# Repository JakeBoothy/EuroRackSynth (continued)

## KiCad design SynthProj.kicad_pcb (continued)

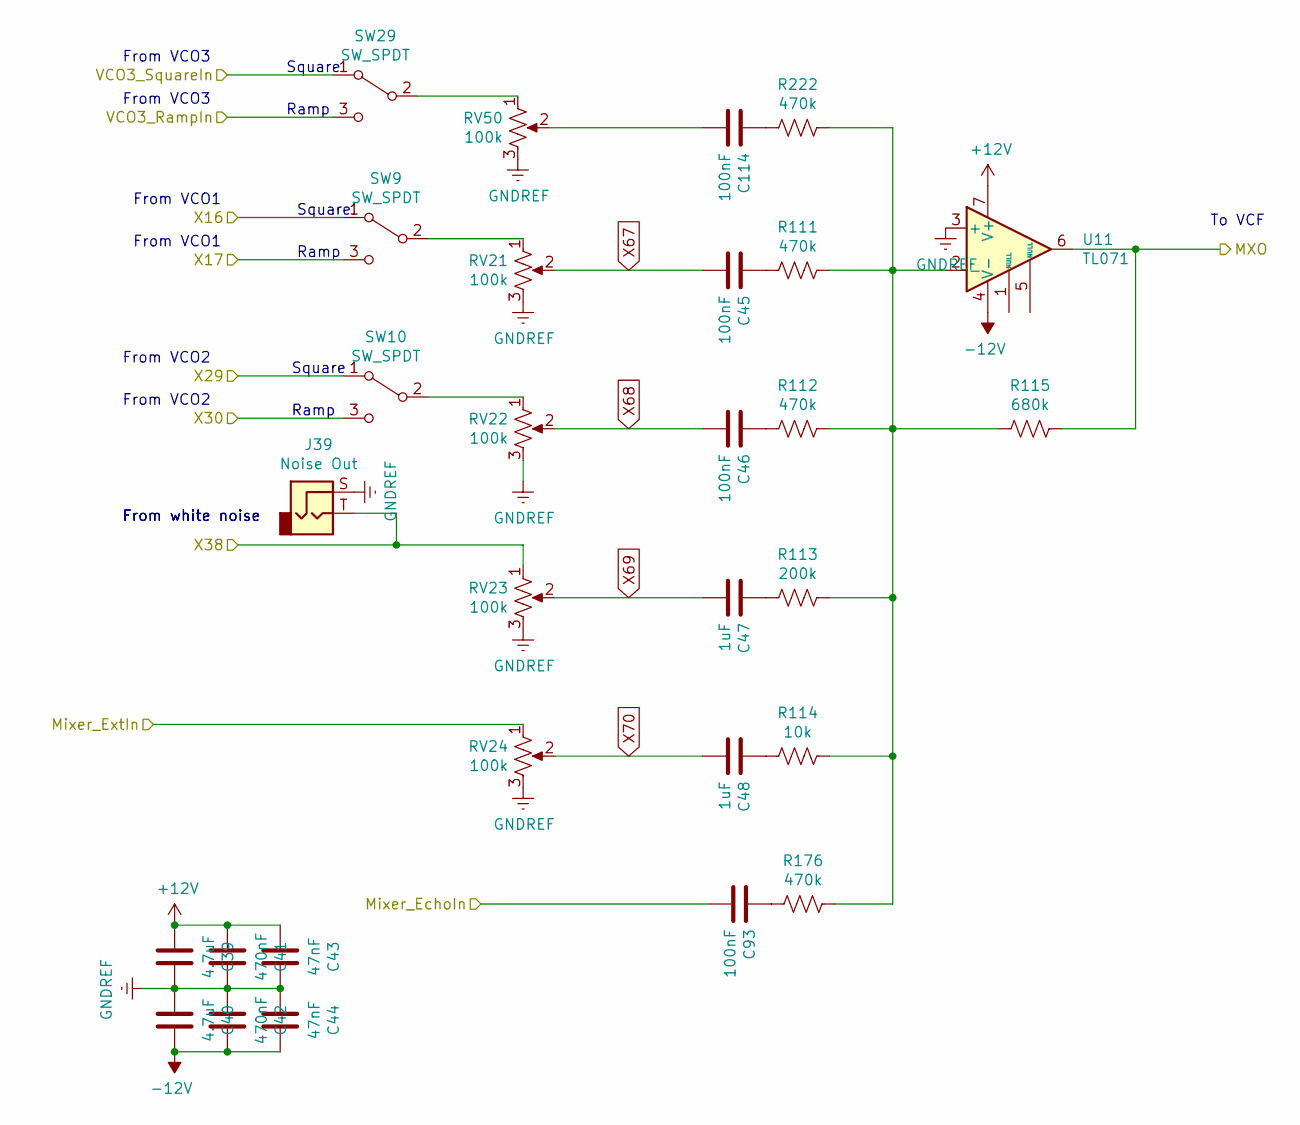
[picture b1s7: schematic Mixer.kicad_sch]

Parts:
C39, C40: 4.7uF; C_0805_2012Metric
C41, C42: 470nF; C_0805_2012Metric
C43, C44: 47nF; C_0603_1608Metric
C45, C46, C93, C114: 100nF; C_0603_1608Metric
C47, C48: 1uF; C_0805_2012Metric
J39: Noise Out; PJ-301-BM
R111, R112, R176, R222: 470k; R_0603_1608Metric
R113: 200k; R_0603_1608Metric
R114: 10k; R_0603_1608Metric
R115: 680k; R_0603_1608Metric
RV21, RV22, RV23, RV24, RV50: 100k; Potentiometer_Alps_RK09K_Single_Vertical
SW9, SW10, SW29: SW_SPDT; SMTS-102
U11: TL071; SO-8_3.9x4.9mm_P1.27mm

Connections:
+12V: C39.2, C41.2, C43.2, U11.7 (V+); also elsewhere on the board
-12V: C40.1, C42.1, C44.1, U11.4 (V-); also elsewhere on the board
/EchoOut: C93.2; also elsewhere on the board
/Mixer/MXO: R115.1, U11.6; also elsewhere on the board
/Mixer/Mixer_ExtIn: RV24.1; also elsewhere on the board
/Mixer/VCO3_RampIn: SW29.3 (C); also elsewhere on the board
/Mixer/VCO3_SquareIn: SW29.1 (A); also elsewhere on the board
/Mixer/X16: SW9.1 (A); also elsewhere on the board
/Mixer/X17: SW9.3 (C); also elsewhere on the board
/Mixer/X29: SW10.1 (A); also elsewhere on the board
/Mixer/X30: SW10.3 (C); also elsewhere on the board
/Mixer/X38: J39.T, RV23.1; also elsewhere on the board
GNDREF: C39.1, C40.2, C41.1, C42.2, C43.1, C44.2, J39.S, RV21.3, RV22.3, RV23.3, RV24.3, RV50.3, U11.3 (+); also elsewhere on the board
unnamed: C45.1, R111.2
unnamed: C46.1, R112.2
unnamed: C47.1, R113.2
unnamed: C48.1, R114.2
unnamed: C93.1, R176.2
unnamed: C114.1, R222.2
unnamed: C114.2, RV50.2
unnamed: RV21.1, SW9.2 (B)
unnamed: RV22.1, SW10.2 (B)
unnamed: RV50.1, SW29.2 (B)
unnamed: R111.1, R112.1, R113.1, R114.1, R115.2, R176.1, R222.1, U11.2 (-)
X67: C45.2, RV21.2
X68: C46.2, RV22.2
X69: C47.2, RV23.2
X70: C48.2, RV24.2

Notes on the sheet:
Ramp
To VCF
From VCO1
From VCO3
Square
From VCO2
From white noise

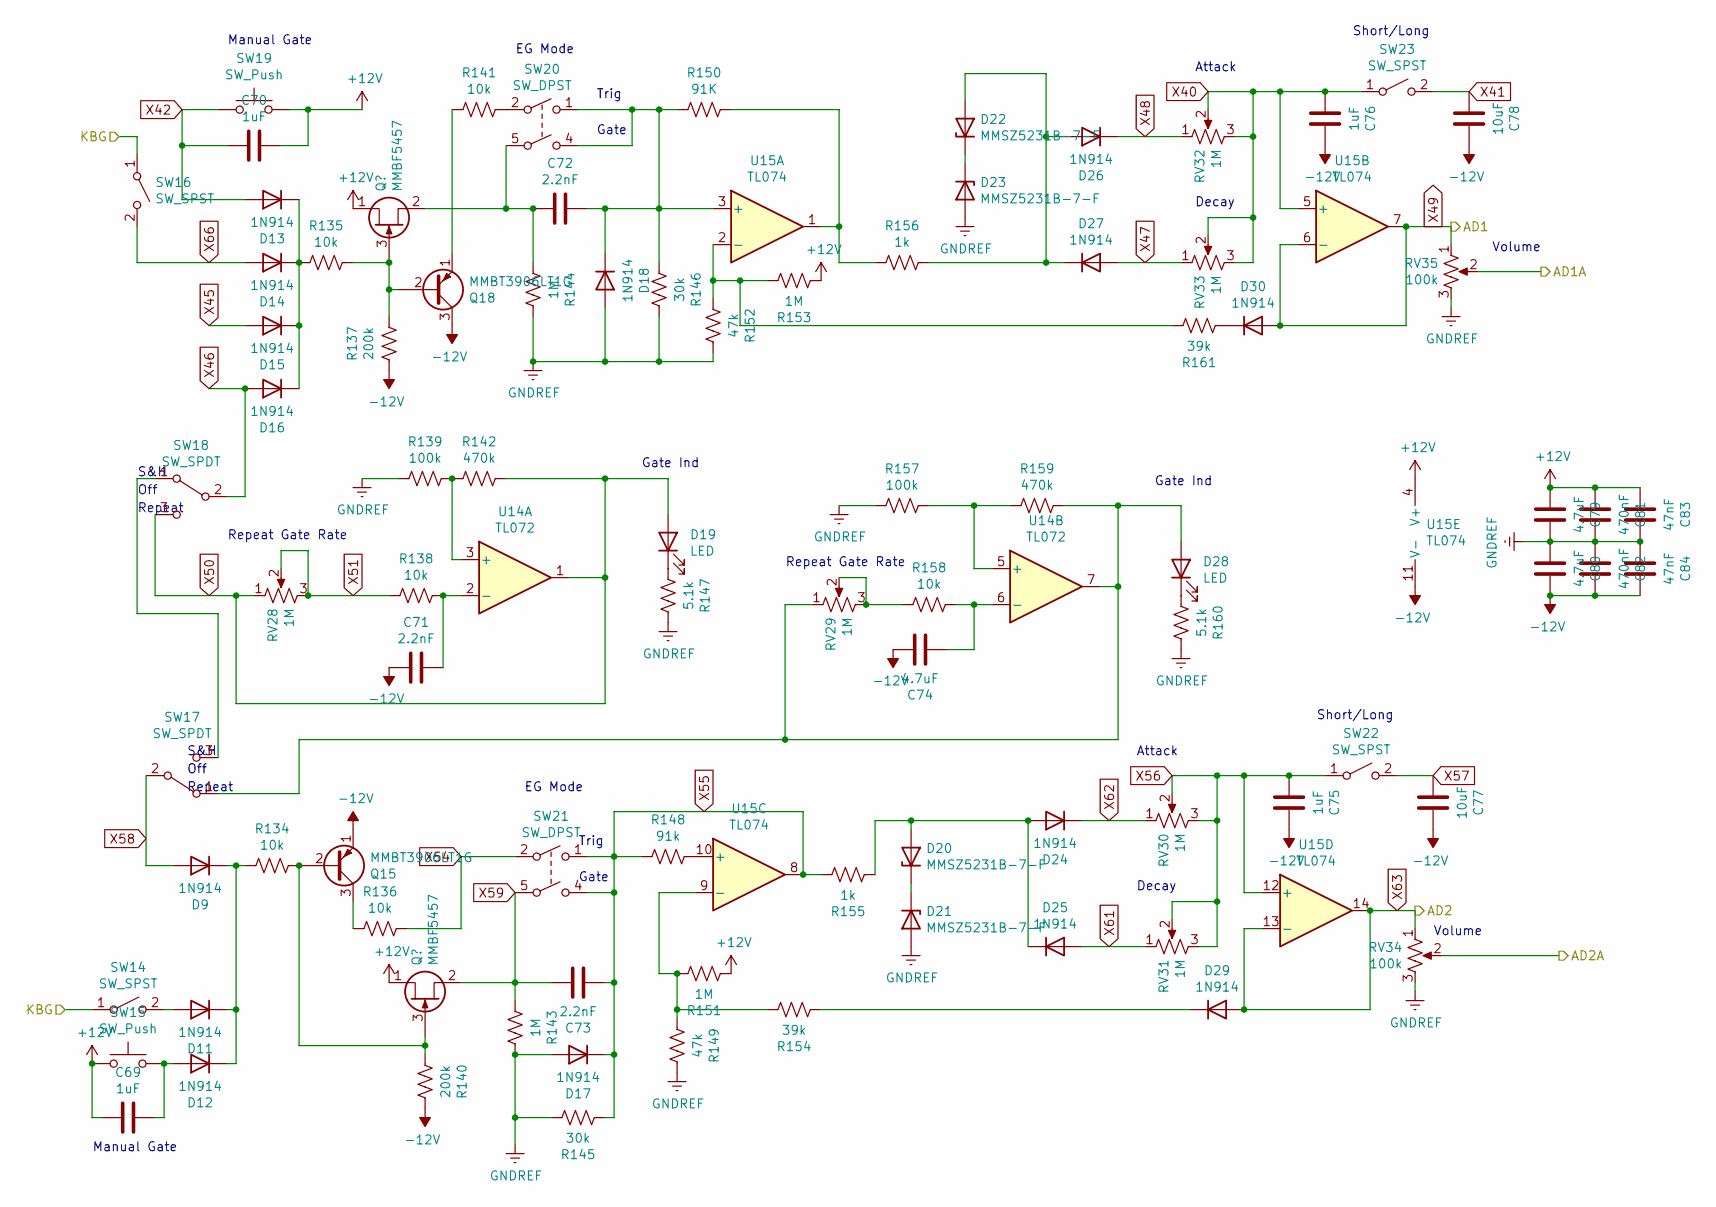
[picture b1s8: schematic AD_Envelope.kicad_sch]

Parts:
C69, C70, C75, C76: 1uF; C_0805_2012Metric
C71, C72, C73: 2.2nF; C_0603_1608Metric
C74, C79, C80: 4.7uF; C_0805_2012Metric
C77, C78: 10uF; C_0805_2012Metric
C81, C82: 470nF; C_0805_2012Metric
C83, C84: 47nF; C_0603_1608Metric
D9, D11, D12, D13, D14, D15, D16, D17, D18, D24, D25, D26, D27, D29, D30: 1N914; D_SOD-323F
D19, D28: LED; LED_0805_2012Metric
D20, D21, D22, D23: MMSZ5231B-7-F; D_SOD-123
Q15, Q18: MMBT3906LT1G; SOT-23-3
Q16, Q17: MMBF5457; SOT-23-3
R134, R135, R136, R138, R141, R158: 10k; R_0603_1608Metric
R137, R140: 200k; R_0603_1608Metric
R139, R157: 100k; R_0603_1608Metric
R142, R159: 470k; R_0603_1608Metric
R143, R144, R151, R153: 1M; R_0603_1608Metric
R145, R146: 30k; R_0603_1608Metric
R147, R160: 5.1k; R_0603_1608Metric
R148: 91k; R_0603_1608Metric
R149, R152: 47k; R_0603_1608Metric
R150: 91K; R_0603_1608Metric
R154, R161: 39k; R_0603_1608Metric
R155, R156: 1k; R_0603_1608Metric
RV28, RV29, RV30, RV31, RV32, RV33: 1M; Potentiometer_Alps_RK09K_Single_Vertical
RV34, RV35: 100k; Potentiometer_Alps_RK09K_Single_Vertical
SW14, SW16, SW22, SW23: SW_SPST; SMTS-102
SW15, SW19: SW_Push; SW_PUSH_6mm_H13mm
SW17, SW18: SW_SPDT; SMTS-102
SW20, SW21: SW_DPST; SMTS-202
U14: TL072; SOP-8_3.9x4.9mm_P1.27mm
U15: TL074; SO-14_3.9x8.65mm_P1.27mm

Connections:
+12V: C69.1, C70.1, C79.2, C81.2, C83.2, Q16.1 (D), Q17.1 (D), R151.2, R153.2, SW15.1, SW19.2, U15.4 (V+); also elsewhere on the board
-12V: C71.2, C74.1, C75.1, C76.1, C77.1, C78.1, C80.1, C82.1, C84.1, Q15.1 (E), Q18.3 (C), R137.2, R140.1, U15.11 (V-); also elsewhere on the board
AD1: D30.2 (A), RV35.1, U15.6 (-), U15.7; also elsewhere on the board
AD1A: RV35.2; also elsewhere on the board
AD2: D29.2 (A), RV34.1, U15.13 (-), U15.14; also elsewhere on the board
AD2A: RV34.2; also elsewhere on the board
GNDREF: C79.1, C80.2, C81.1, C82.2, C83.1, C84.2, D17.2 (A), D18.2 (A), D21.2 (A), D23.2 (A), R139.2, R143.1, R144.1, R145.1, R146.1, R147.1, R149.1, R152.1, R157.2, R160.1, RV34.3, RV35.3; also elsewhere on the board
KBG: SW14.1 (A), SW16.1 (A); also elsewhere on the board
unnamed: D9.1 (K), D11.1 (K), D12.1 (K), R134.2
unnamed: D11.2 (A), SW14.2 (B)
unnamed: C69.2, D12.2 (A), SW15.2
unnamed: D13.1 (K), D14.1 (K), D15.1 (K), D16.1 (K), R135.2
unnamed: C72.1, D18.1 (K), R146.2, R150.2, SW20.1, SW20.4, U15.3 (+)
unnamed: D19.1 (K), R147.2
unnamed: D20.2 (A), D24.2 (A), D25.1 (K), R155.2
unnamed: D20.1 (K), D21.1 (K)
unnamed: D22.2 (A), D26.2 (A), D27.1 (K), R156.1
unnamed: D22.1 (K), D23.1 (K)
unnamed: D28.2 (A), R159.1, RV29.1, SW17.1 (A), U14.7
unnamed: D28.1 (K), R160.2
unnamed: D29.1 (K), R154.2
unnamed: D30.1 (K), R161.2
unnamed: Q15.2 (B), Q17.3 (G), R134.1, R140.2
unnamed: Q15.3 (C), R136.2
unnamed: Q16.3 (G), Q18.2 (B), R135.1, R137.1
unnamed: C72.2, Q16.2 (S), R144.2, SW20.5
unnamed: Q18.1 (E), R141.2
unnamed: R141.1, SW20.2
unnamed: R150.1, R156.2, U15.1
unnamed: R158.2, RV29.2, RV29.3
unnamed: SW17.3 (C), SW18.1 (A)
unnamed: R139.1, R142.2, U14.3 (+)
unnamed: C71.1, R138.1, U14.2 (-)
unnamed: R157.1, R159.2, U14.5 (+)
unnamed: C74.2, R158.1, U14.6 (-)
unnamed: R152.2, R153.1, R161.1, U15.2 (-)
unnamed: R148.1, U15.10 (+)
unnamed: R149.2, R151.1, R154.1, U15.9 (-)
X40: C76.2, RV32.2, RV32.3, RV33.2, RV33.3, SW23.1 (A), U15.5 (+)
X41: C78.2, SW23.2 (B)
X42: C70.2, D13.2 (A), SW19.1
X45: D15.2 (A)
X46: D16.2 (A), SW18.2 (B)
X47: D27.2 (A), RV33.1
X48: D26.1 (K), RV32.1
X50: D19.2 (A), R142.1, RV28.1, SW18.3 (C), U14.1
X51: R138.2, RV28.2, RV28.3
X54: R136.1, SW21.2
X55: C73.2, D17.1 (K), R145.2, R148.2, R155.1, SW21.1, SW21.4, U15.8
X56: C75.2, RV30.2, RV30.3, RV31.2, RV31.3, SW22.1 (A), U15.12 (+)
X57: C77.2, SW22.2 (B)
X58: D9.2 (A), SW17.2 (B)
X59: C73.1, Q17.2 (S), R143.2, SW21.5
X61: D25.2 (A), RV31.1
X62: D24.1 (K), RV30.1
X66: D14.2 (A), SW16.2 (B)

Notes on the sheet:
Gate Ind
S&H
Short/Long
Trig
Volume
EG Mode
Manual Gate
Gate
Decay
Repeat
Attack
Off
Repeat Gate Rate

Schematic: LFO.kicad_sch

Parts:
C61: 22nF; C_0603_1608Metric
C62: 10pF; C_0603_1608Metric
C63, C64: 4.7uF; C_0805_2012Metric
C65, C66: 470nF; C_0805_2012Metric
C67, C68: 47nF; C_0603_1608Metric
D6, D7: 1N914; D_SOD-323F
D8: LED; LED_0805_2012Metric
Q14: MMBT3904-7-F; SOT-23-3
R123: 1k; R_0603_1608Metric
R124, R128: 100k; R_0603_1608Metric
R125: 3M; R_0603_1608Metric
R126: 220; R_0603_1608Metric
R127: 3.9k; R_0603_1608Metric
R129: 2.2k; R_0603_1608Metric
R130: 130k; R_0603_1608Metric
R131: 9.1k; R_0603_1608Metric
R132: 10k; R_0603_1608Metric
R133: 270k; R_0603_1608Metric
RV26: 10k; Potentiometer_Alps_RK09K_Single_Vertical
RV27: 100k; Potentiometer_Alps_RK09K_Single_Vertical
SW11: SW_SPDT; SMTS-102
SW12: SMTS-103-A1-T0; SMTS-102
SW13: SW_Push_DPDT; SMTS-202
U13: TL072; SOP-8_3.9x4.9mm_P1.27mm

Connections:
+12V: C63.2, C65.2, C67.2, R127.1, U13.8 (V+); also elsewhere on the board
-12V: C64.1, C66.1, C68.1, U13.4 (V-); also elsewhere on the board
/LFO/LFO: RV27.1, SW13.5 (B); also elsewhere on the board
GNDREF: C63.1, C64.2, C65.1, C66.2, C67.1, C68.2, D8.1 (K), R126.2, R131.2, RV27.3, U13.2 (-), U13.5 (+); also elsewhere on the board
LFO1A: RV27.2; also elsewhere on the board
unnamed: C61.2, R128.2, R129.2, R130.2, U13.7
unnamed: C62.2, R132.1, R133.1, RV26.1, SW13.2 (B), U13.1
unnamed: D6.2 (A), D7.1 (K), R123.1
unnamed: D6.1 (K), SW12.1 (A)
unnamed: D7.2 (A), SW12.3 (C)
unnamed: D8.2 (A), Q14.1 (E)
unnamed: Q14.2 (B), R128.1
unnamed: Q14.3 (C), R127.2
unnamed: R126.1, RV26.3
unnamed: R129.1, SW13.4 (A)
unnamed: R131.1, R132.2, SW13.6 (C)
unnamed: R124.1, SW11.1 (A)
unnamed: R125.1, RV26.2, SW11.2 (B)
unnamed: SW12.2 (B), SW13.1 (A)
unnamed: C62.1, R130.1, R133.2, U13.3 (+)
unnamed: C61.1, R123.2, R124.2, R125.2, U13.6 (-)

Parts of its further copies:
C106: 22nF; C_0603_1608Metric
C107: 10pF; C_0603_1608Metric
C108, C109: 4.7uF; C_0805_2012Metric
C110, C111: 470nF; C_0805_2012Metric
C112, C113: 47nF; C_0603_1608Metric
D36, D37: 1N914; D_SOD-323F
D38: LED; LED_0805_2012Metric
Q27: MMBT3904-7-F; SOT-23-3
R211: 1k; R_0603_1608Metric
R212, R216: 100k; R_0603_1608Metric
R213: 3M; R_0603_1608Metric
R214: 220; R_0603_1608Metric
R215: 3.9k; R_0603_1608Metric
R217: 2.2k; R_0603_1608Metric
R218: 130k; R_0603_1608Metric
R219: 9.1k; R_0603_1608Metric
R220: 10k; R_0603_1608Metric
R221: 270k; R_0603_1608Metric
RV48: 10k; Potentiometer_Alps_RK09K_Single_Vertical
RV49: 100k; Potentiometer_Alps_RK09K_Single_Vertical
SW26: SW_SPDT; SMTS-102
SW27: SMTS-103-A1-T0; SMTS-102
SW28: SW_Push_DPDT; SMTS-202
U20: TL072; SOP-8_3.9x4.9mm_P1.27mm

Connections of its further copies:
+12V: C108.2, C110.2, C112.2, R215.1, U20.8 (V+); also elsewhere on the board
-12V: C109.1, C111.1, C113.1, U20.4 (V-); also elsewhere on the board
/LFO1/LFO: RV49.1, SW28.5 (B)
GNDREF: C108.1, C109.2, C110.1, C111.2, C112.1, C113.2, D38.1 (K), R214.2, R219.2, RV49.3, U20.2 (-), U20.5 (+); also elsewhere on the board
LFO2A: RV49.2; also elsewhere on the board
unnamed: C106.2, R216.2, R217.2, R218.2, U20.7
unnamed: C107.2, R220.1, R221.1, RV48.1, SW28.2 (B), U20.1
unnamed: D36.2 (A), D37.1 (K), R211.1
unnamed: D36.1 (K), SW27.1 (A)
unnamed: D37.2 (A), SW27.3 (C)
unnamed: D38.2 (A), Q27.1 (E)
unnamed: Q27.2 (B), R216.1
unnamed: Q27.3 (C), R215.2
unnamed: R214.1, RV48.3
unnamed: R217.1, SW28.4 (A)
unnamed: R219.1, R220.2, SW28.6 (C)
unnamed: R212.1, SW26.1 (A)
unnamed: R213.1, RV48.2, SW26.2 (B)
unnamed: SW27.2 (B), SW28.1 (A)
unnamed: C107.1, R218.1, R221.2, U20.3 (+)
unnamed: C106.1, R211.2, R212.2, R213.2, U20.6 (-)

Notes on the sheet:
Triangle
Ramp
Square
Falling
Ramp/Square Select
Rising
Low
SPDT On-Off-On SMTS-103-A1-T0
Range
Ramp Shape

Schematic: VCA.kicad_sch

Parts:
C35, C36: 470nF; C_0805_2012Metric
C37, C38: 10uF; C_0805_2012Metric
R98: 3k; R_0603_1608Metric
R99: 2k; R_0603_1608Metric
R100, R101: 62k; R_0603_1608Metric
R102, R104: 100k; R_0603_1608Metric
R103: 220; R_0603_1608Metric
R105: 110k; R_0603_1608Metric
R106, R109: 10k; R_0603_1608Metric
R107: 4.7k; R_0603_1608Metric
R108: 6.2k; R_0603_1608Metric
R110: 47k; R_0603_1608Metric
RV18, RV19, RV20: 100k; Potentiometer_Alps_RK09K_Single_Vertical
SW8: SW_SPDT; SMTS-102
U9: LM13700; SO-16_5.3x10.2mm_P1.27mm
U10: TL072; SO-8_3.9x4.9mm_P1.27mm

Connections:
+12V: C35.2, R98.2, U9.11 (V+), U10.8 (V+); also elsewhere on the board
-12V: C36.1, U9.6 (V-), U10.4 (V-); also elsewhere on the board
/LFO/LFO: SW8.3 (C); also elsewhere on the board
/VCA/Main_Out: RV20.2; also elsewhere on the board
/VCA/VCO1: SW8.1 (A)
/VCA/X84: C37.2; also elsewhere on the board
AD2: RV18.1; also elsewhere on the board
GNDREF: C35.1, C36.2, R99.1, R103.1, R105.2, R107.1, R108.2, RV19.3, RV20.3, U9.13 (-), U10.3 (+), U10.5 (+); also elsewhere on the board
unnamed: C37.1, R102.2
unnamed: C38.2, R107.2, U9.9
unnamed: R98.1, R99.2, RV18.3
unnamed: R104.1, R106.2, U10.1
unnamed: R105.1, U9.10, U9.12
unnamed: R108.1, R110.2, U9.16
unnamed: R109.1, R110.1, U10.7
unnamed: RV19.1, SW8.2 (B)
unnamed: R102.1, R103.2, U9.14 (+)
unnamed: R100.1, R101.1, R104.2, U10.2 (-)
unnamed: R106.1, R109.2, U10.6 (-)
X81: R100.2, RV19.2
X82: R101.2, RV18.2
X85: C38.1, RV20.1

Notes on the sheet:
VCA AD Modulation
From LFO1
From VCO1
Master Volume
VCA Modulation
Bypass

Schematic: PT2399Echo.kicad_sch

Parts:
C135, C136, C141, C147: 4.7uF; C_0805_2012Metric
C137, C138, C142: 470nF; C_0805_2012Metric
C139, C140, C143: 47nF; C_0603_1608Metric
C144: 47uF; C_0805_2012Metric
C145, C146, C150, C152, C157: 100nF; C_0603_1608Metric
C148, C155, C156, C158, C159, C161: 1uF; C_0805_2012Metric
C151: 100pF; C_0603_1608Metric
C153, C154: 560pF; C_0603_1608Metric
C160: 22pF; C_0603_1608Metric
C162: 10uF; C_0805_2012Metric
D82, D83: 1N914; D_SOD-323F
Q21, Q22: MMBT3904-7-F; SOT-23-3
Q23, Q24: MMBT3906LT1G; SOT-23-3
R263, R264, R275, R276, R283, R288, R295, R298: 100k; R_0603_1608Metric
R265, R268, R290, R294: 1k; R_0603_1608Metric
R266, R291, R292: 200k; R_0603_1608Metric
R269: 680k; R_0603_1608Metric
R270: 270k; R_0603_1608Metric
R273: 1M; R_0603_1608Metric
R277, R278, R281, R284, R285, R293: 20k; R_0603_1608Metric
R279: 3k; R_0603_1608Metric
R280, R287: 43k; R_0603_1608Metric
R282, R289: 15k; R_0603_1608Metric
R286, R300, R303: 4.7k; R_0603_1608Metric
R296: 18k; R_0603_1608Metric
R297, R302: 47k; R_0603_1608Metric
R299, R301, R304: 470k; R_0603_1608Metric
RV51, RV74, RV76, RV77, RV78: 100k; Potentiometer_Alps_RK09K_Single_Vertical
U28, U29: TL074; SO-14_3.9x8.65mm_P1.27mm
U30: LM13700; SO-16_5.3x10.2mm_P1.27mm
U31: PT2399; SOP-16_4.55x10.3mm_P1.27mm

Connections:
+5V: C141.2, C142.2, C143.2, RV74.1, RV76.1, RV77.3, U31.1 (VCC); also elsewhere on the board
+12V: C135.2, C137.2, C139.2, R266.2, R273.1, R301.1, R304.1, U28.4 (V+), U29.4 (V+), U30.11 (V+); also elsewhere on the board
-5V: R269.2, RV74.3, RV76.3, RV77.1
-12V: C136.1, C138.1, C140.1, R300.1, R303.1, U28.11 (V-), U29.11 (V-), U30.6 (V-); also elsewhere on the board
/PT2399Echo/EchoOut: C162.2; also elsewhere on the board
/PT2399Echo/Echo_A: C155.1, R297.1, R301.2, U30.7, U30.12
/PT2399Echo/Echo_B: C161.2, R302.1, R304.2, U30.5, U30.10
/PT2399Echo/Echo_C: Q23.1 (E), U30.1
/PT2399Echo/Echo_CV_Input: R276.1; also elsewhere on the board
/PT2399Echo/Echo_DT_CV_Input: R264.2; also elsewhere on the board
/PT2399Echo/Echo_ExtIn: RV51.1; also elsewhere on the board
/PT2399Echo/Echo_Repeat_CV_Input: R283.2; also elsewhere on the board
/PT2399Echo/VR2: C147.2, R269.1, R270.2, U28.5 (+), U29.10 (+)
GNDREF: C135.1, C136.2, C137.1, C138.2, C139.1, C140.2, C141.1, C142.1, C143.1, C144.1, C145.2, C146.2, C147.1, C157.1, Q22.2 (B), R270.1, R282.2, R289.1, R290.2, R293.2, R294.2, R296.2, R297.2, R302.2, RV51.3, RV78.3, U28.10 (+), U28.12 (+), U30.4 (-), U30.13 (-), U31.3 (AGND), U31.4 (DGND); also elsewhere on the board
unnamed: C148.2, RV51.2
unnamed: C151.1, R279.1, U28.8
unnamed: C155.2, R284.2
unnamed: C156.2, R285.2
unnamed: C157.2, C159.2, R286.1
unnamed: C158.2, RV78.1
unnamed: C159.1, R291.2, R292.1
unnamed: C160.1, C162.1, R299.1, U29.7
unnamed: C161.1, R298.2
unnamed: D82.2 (A), Q23.2 (B), U29.1
unnamed: D82.1 (K), Q23.3 (C), R282.1, U29.2 (-)
unnamed: D83.2 (A), Q24.2 (B), U29.14
unnamed: D83.1 (K), Q24.3 (C), R289.2, U29.13 (-)
unnamed: Q21.2 (B), R268.1, U28.14
unnamed: C151.2, Q21.3 (C), R273.2, U28.9 (-)
unnamed: Q21.1 (E), Q22.1 (E), R279.2
unnamed: Q22.3 (C), R265.2
unnamed: Q24.1 (E), U30.16
unnamed: R263.2, RV74.2
unnamed: R275.1, RV76.2
unnamed: R288.1, RV77.2
unnamed: R295.1, RV78.2
unnamed: R300.2, U30.8
unnamed: R303.2, U30.9
unnamed: C148.1, U28.3 (+)
unnamed: C156.1, C158.1, U28.1, U28.2 (-)
unnamed: R275.2, R276.2, R280.1, U28.6 (-)
unnamed: R263.1, R264.1, R266.1, R268.2, U28.13 (-)
unnamed: R280.2, U28.7, U29.3 (+)
unnamed: R293.1, R295.2, R298.1, U29.5 (+)
unnamed: C160.2, R296.1, R299.2, U29.6 (-)
unnamed: R283.1, R287.1, R288.2, U29.9 (-)
unnamed: R287.2, U29.8, U29.12 (+)
unnamed: R290.1, R292.2, U30.14 (+)
unnamed: R291.1, R294.1, U30.3 (+)
unnamed: C146.1, U31.8 (CC0)
unnamed: C145.1, U31.7 (CC1)
unnamed: C153.2, R277.1, R284.1, R285.1, U31.16 (LPF1-IN)
unnamed: C153.1, R277.2, U31.15 (LPF1-OUT)
unnamed: C154.1, R278.1, R281.2, U31.13 (LPF2-IN)
unnamed: C154.2, R281.1, R286.2, U31.14 (LPF2-OUT)
unnamed: C150.2, U31.10 (OP1-IN)
unnamed: C150.1, U31.9 (OP1-OUT)
unnamed: C152.1, U31.11 (OP2-IN)
unnamed: C152.2, R278.2, U31.12 (OP2-OUT)
unnamed: C144.2, U31.2 (REF)
unnamed: R265.1, U31.6 (VCO)

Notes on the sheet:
Buffered Input
Original Level Adjust
Echo Level Adjust
Repeat Adjust
Input Level
Delay Time Adjust

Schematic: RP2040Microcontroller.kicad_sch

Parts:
C195, C196: 27pF; C_0603_1608Metric
C197, C200, C201: 10uF; C_0805_2012Metric
C198, C199, C202, C203, C205, C207, C208, C209, C210, C211, C212, C213, C214, C215, C216: 100nF; C_0603_1608Metric
C204, C206: 1uF; C_0805_2012Metric
D100: 1N914; D_SOD-323F
D101, D102, D103, D104, D105, D106, D107, D108, D109, D110, D111, D112, D113, D114, D115, D116: LED; LED_0805_2012Metric
J5: Conn_01x18; Hirose_FH12-18S-0.5SH_1x18-1MP_P0.50mm_Horizontal
J15: Micro_SD_Card
J40, J43: Conn_01x02; PinHeader_1x02_P2.54mm_Vertical
J41: DIN-504D-M5; SD-50BV
J42: USB_B; USB_B_TE_5787834_Vertical
R346: 220; R_0603_1608Metric
R347, R348, R351: 1k; R_0603_1608Metric
R349: DNF; C_0402_1005Metric
R350: 4.7k; R_0603_1608Metric
R357, R359, R360: 100k; R_0603_1608Metric
R361, R362: 27; R_0603_1608Metric
R363, R364, R365, R366, R367, R368, R369, R370, R371, R372, R373, R374, R375, R376, R377, R378: 470; R_0603_1608Metric
R379: 412; R_0603_1608Metric
R380, R384, R385, R386, R388: 1.65k; R_0603_1608Metric
R381, R382, R383, R387: 10.7k; R_0603_1608Metric
R389, R390, R391, R392, R393, R394, R395: 10k; R_0603_1608Metric
R396, R397, R398: 66.5k; R_0603_1608Metric
R399, R400, R401: 28.7k; R_0603_1608Metric
RV40, RV41, RV42: 100k; Potentiometer_Alps_RK09K_Single_Vertical
SW56, SW58: SW_Push; SW_PUSH_6mm_H13mm
TP1, TP2, TP3, TP4, TP5, TP6: TestPoint; TestPoint_Pad_D1.0mm
U40: 6N138; SOP-8_6.605x9.655mm_P2.54mm
U41: NCP1117-3.3_SOT223; SOT-223-3_TabPin2
U42: W25Q128JVS; SOIC-8_5.23x5.23mm_P1.27mm
U43: RP2040; RP2040-QFN-56
U44: MCP23017_SS; SSOP-28_5.3x10.2mm_P0.65mm
U45: REF3012; SOT-23
U46: MCP4728; MSOP-10_3x3mm_P0.5mm
U47, U49: TL074; SO-14_3.9x8.65mm_P1.27mm
U48: CD74HC4067SM; SSOP-24_5.3x8.2mm_P0.65mm
Y1: ABLS-12.000MHZ-B4-T; Crystal_SMD_HC49-US

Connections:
+1V1: C202.1, C203.1, C204.1, U43.23 (DVDD), U43.45 (VREG_VOUT), U43.50 (DVDD)
+3V3: C199.1, C200.1, C201.1, C205.1, C206.1, C207.1, C208.1, C209.1, C210.1, C211.1, C212.1, R349.1, R351.2, R357.2, R359.2, R360.2, R363.1, R364.1, R365.1, R366.1, R367.1, R368.1, R369.1, R370.1, R371.1, R372.1, R373.1, R374.1, R375.1, R376.1, R377.1, R378.1, RV40.3, RV41.3, RV42.3, U41.2 (VO), U42.8 (VCC), U43.1 (IOVDD), U43.10 (IOVDD), U43.22 (IOVDD), U43.33 (IOVDD), U43.42 (IOVDD), U43.43 (ADC_AVDD), U43.44 (VREG_IN), U43.48 (USB_VDD), U43.49 (IOVDD), U44.9 (VDD), U46.1 (VDD), U48.24 (VCC); also elsewhere on the board
+5V: C198.1, U40.8 (VCC), U45.1 (IN); also elsewhere on the board
+12V: U47.4 (V+); also elsewhere on the board
-12V: U47.11 (V-); also elsewhere on the board
/RP2040Microcontroller/GPIO0: J43.1, U43.2 (GPIO0)
/RP2040Microcontroller/GPIO1: J43.2, U43.3 (GPIO1)
/RP2040Microcontroller/GPIO2: U43.4 (GPIO2)
/RP2040Microcontroller/GPIO3: U43.5 (GPIO3)
/RP2040Microcontroller/GPIO4: U43.6 (GPIO4)
/RP2040Microcontroller/GPIO5: U43.7 (GPIO5)
/RP2040Microcontroller/GPIO6: U43.8 (GPIO6), U44.12 (SCK), U46.3 (SDA)
/RP2040Microcontroller/GPIO7: U43.9 (GPIO7), U44.13 (SDA), U46.2 (SCL)
/RP2040Microcontroller/GPIO8: U43.11 (GPIO8)
/RP2040Microcontroller/GPIO9: R351.1, U40.6 (VO2), U43.12 (GPIO9)
/RP2040Microcontroller/GPIO10: U43.13 (GPIO10)
/RP2040Microcontroller/GPIO11: U43.14 (GPIO11)
/RP2040Microcontroller/GPIO12: U43.15 (GPIO12)
/RP2040Microcontroller/GPIO13: U43.27 (GPIO16), U48.10 (S0)
/RP2040Microcontroller/GPIO14: U43.18 (GPIO15), U48.11 (S1)
/RP2040Microcontroller/GPIO15: U43.17 (GPIO14), U48.14 (S2)
/RP2040Microcontroller/GPIO16: U43.16 (GPIO13), U48.13 (S3)
/RP2040Microcontroller/GPIO17: R359.1, SW58.1, U43.36 (GPIO24)
/RP2040Microcontroller/GPIO18: U43.35 (GPIO23)
/RP2040Microcontroller/GPIO19: R357.1, SW56.1, U43.34 (GPIO22)
/RP2040Microcontroller/GPIO20: U43.32 (GPIO21)
/RP2040Microcontroller/GPIO21: U43.31 (GPIO20)
/RP2040Microcontroller/GPIO22: U43.30 (GPIO19)
/RP2040Microcontroller/GPIO23: U43.29 (GPIO18)
/RP2040Microcontroller/GPIO24: U43.28 (GPIO17)
/RP2040Microcontroller/GPIO25: U43.37 (GPIO25)
/RP2040Microcontroller/GPIO26_ADC0: U43.41 (GPIO29_ADC3)
/RP2040Microcontroller/GPIO27_ADC1: U43.40 (GPIO28_ADC2)
/RP2040Microcontroller/GPIO28_ADC2: U43.39 (GPIO27_ADC1)
/RP2040Microcontroller/GPIO29_ADC0: R391.1, TP4.1, U47.1
/RP2040Microcontroller/GPIO29_ADC1: R389.1, U47.7
/RP2040Microcontroller/GPIO29_ADC2: R390.1, U47.8
/RP2040Microcontroller/GPIO29_ADC3: U43.38 (GPIO26_ADC0), U48.1 (COM)
/RP2040Microcontroller/QSPI_SCLK: U42.6 (CLK), U43.52 (QSPI_SCLK)
/RP2040Microcontroller/QSPI_SD0: U42.5 (DI(IO0)), U43.53 (QSPI_SD0)
/RP2040Microcontroller/QSPI_SD1: U42.2 (DO(IO1)), U43.55 (QSPI_SD1)
/RP2040Microcontroller/QSPI_SD2: U42.3 (IO2), U43.54 (QSPI_SD2)
/RP2040Microcontroller/QSPI_SD3: U42.7 (IO3), U43.51 (QSPI_SD3)
/RP2040Microcontroller/QSPI_SS: R347.1, R349.2, U42.1 (~CS), U43.56 (QSPI_SS)
/RP2040Microcontroller/RUN: U43.26 (RUN)
/RP2040Microcontroller/SWCLK: U43.24 (SWCLK)
/RP2040Microcontroller/SWD: U43.25 (SWD)
/RP2040Microcontroller/USB_D+: J42.3 (D+), R361.1
/RP2040Microcontroller/USB_D-: J42.2 (D-), R362.1
/RP2040Microcontroller/VIN_A: R398.2, TP6.1; also elsewhere on the board
/RP2040Microcontroller/VIN_B: R396.2; also elsewhere on the board
/RP2040Microcontroller/VIN_C: R397.2; also elsewhere on the board
/RP2040Microcontroller/VOUT_A: R392.1, TP5.1, U49.1; also elsewhere on the board
/RP2040Microcontroller/VOUT_B: R393.1, U49.7; also elsewhere on the board
/RP2040Microcontroller/VOUT_C: R394.1, U49.8; also elsewhere on the board
/RP2040Microcontroller/VOUT_D: R395.1, U47.14; also elsewhere on the board
/RP2040Microcontroller/VREF1.0: R379.1, R380.2, TP1.1, U47.3 (+), U47.5 (+), U47.10 (+)
/RP2040Microcontroller/VREF1.25: R379.2, TP2.1, U45.2 (OUT), U47.13 (-), U49.3 (+), U49.6 (-), U49.9 (-)
/RP2040Microcontroller/XIN: C195.1, U43.20 (XIN), Y1.1
/RP2040Microcontroller/XOUT: R348.1, U43.21 (XOUT)
/RP2040Microcontroller/~USB_BOOT: J40.1, R347.2
GNDD: C195.2, C196.2, C197.2, C198.2, C199.2, C200.2, C201.2, C202.2, C203.2, C204.2, C205.2, C206.2, C207.2, C208.2, C209.2, C210.2, C211.2, C212.2, J40.2, J42.4 (GND), J42.5 (Shield), R350.2, SW56.2, SW58.2, U40.5 (GND), U41.1 (GND), U42.4 (GND), U43.19 (TESTEN), U43.57 (GND), U46.10 (VSS)
GNDREF: R380.1, R381.1, R382.1, R383.1, R387.1, R399.2, R400.2, R401.2, RV40.1, RV41.1, RV42.1, U44.10 (VSS), U44.15 (A0), U44.16 (A1), U44.17 (A2), U45.3 (GND), U48.12 (GND), U48.15 (~E); also elsewhere on the board
unnamed: C196.1, R348.2, Y1.2
unnamed: C213.1, R384.1
unnamed: C214.1, R385.1
unnamed: C215.1, R386.1
unnamed: C216.1, R388.1
unnamed: D100.2 (A), R346.1, U40.3 (C2)
unnamed: D100.1 (K), J41.4, U40.2 (C1)
unnamed: D101.2 (A), R363.2
unnamed: D101.1 (K), U44.1 (GPB0)
unnamed: D102.2 (A), R364.2
unnamed: D102.1 (K), U44.2 (GPB1)
unnamed: D103.2 (A), R365.2
unnamed: D103.1 (K), U44.3 (GPB2)
unnamed: D104.2 (A), R366.2
unnamed: D104.1 (K), U44.4 (GPB3)
unnamed: D105.2 (A), R367.2
unnamed: D105.1 (K), U44.5 (GPB4)
unnamed: D106.2 (A), R368.2
unnamed: D106.1 (K), U44.6 (GPB5)
unnamed: D107.2 (A), R369.2
unnamed: D107.1 (K), U44.7 (GPB6)
unnamed: D108.2 (A), R370.2
unnamed: D108.1 (K), U44.8 (GPB7)
unnamed: D109.2 (A), R371.2
unnamed: D109.1 (K), U44.21 (GPA0)
unnamed: D110.2 (A), R372.2
unnamed: D110.1 (K), U44.22 (GPA1)
unnamed: D111.2 (A), R373.2
unnamed: D111.1 (K), U44.23 (GPA2)
unnamed: D112.2 (A), R374.2
unnamed: D112.1 (K), U44.24 (GPA3)
unnamed: D113.2 (A), R375.2
unnamed: D113.1 (K), U44.25 (GPA4)
unnamed: D114.2 (A), R376.2
unnamed: D114.1 (K), U44.26 (GPA5)
unnamed: D115.2 (A), R377.2
unnamed: D115.1 (K), U44.27 (GPA6)
unnamed: D116.2 (A), R378.2
unnamed: D116.1 (K), U44.28 (GPA7)
unnamed: J41.5, R346.2
unnamed: R350.1, U40.7 (VO1)
unnamed: R362.2, U43.46 (USB_DM)
unnamed: R361.2, U43.47 (USB_DP)
unnamed: R360.1, U44.18 (~RESET)
unnamed: C213.2, TP3.1, U46.6 (VOUTA)
unnamed: C214.2, U46.7 (VOUTB)
unnamed: C215.2, U46.8 (VOUTC)
unnamed: C216.2, U46.9 (VOUTD)
unnamed: R391.2, R398.1, R401.1, U47.2 (-)
unnamed: R389.2, R396.1, R399.1, U47.6 (-)
unnamed: R390.2, R397.1, R400.1, U47.9 (-)
unnamed: R382.2, R388.2, R395.2, U47.12 (+)
unnamed: RV40.2, U48.8 (I1)
unnamed: RV41.2, U48.7 (I2)
unnamed: RV42.2, U48.6 (I3)
unnamed: R384.2, R387.2, R392.2, U49.2 (-)
unnamed: R383.2, R385.2, R393.2, U49.5 (+)
unnamed: R381.2, R386.2, R394.2, U49.10 (+)
VBUS: C197.1, J42.1 (VBUS), U41.3 (VI)

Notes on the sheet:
TFTCS
+-10V Out
Make sure R3 and R4 are close to RP2040
Voltage References
+-10V in
TSCS
Power
0-3.3V Out
0-3.3V In
8 LEDS for the pushbuttons
INT
MISO
SCL
ADC In
EYESPI Display Connector
IOs
MEM_CS
Analog Mux Data
GPIO1
BUSY
TFTRST
Flash
Potentiometer Inputs
SCK
DAC
Make sure C10 is close to pin 44 of RP2040
Analog Mux In
Quad ADC Input
Debug
VCC
Midi Input
Crystal
Midi/UARTRX
CARDCS
MOSI
Quad I2C DAC Output
Make sure C8 is close to pin 45 of RP2040
LITE
GND
SDA

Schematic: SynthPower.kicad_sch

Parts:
C217, C218, C223, C227, C228: 4.7uF; C_0805_2012Metric
C219, C220, C224, C226, C229: 470nF; C_0805_2012Metric
C221, C222, C225: 47nF; C_0603_1608Metric
J29: Conn_01x16_Pin
J44: Jack-DC; BarrelJack_CUI_PJ-063AH_Horizontal
J45: Conn_01x10_Pin
L1: L; L_7.3x7.3_H3.5
R405, R406: 10k; R_0603_1608Metric
R407: 105; R_0603_1608Metric
R408: 20k; R_0603_1608Metric
TP7, TP8, TP9, TP12, TP13: TestPoint; TestPoint_Plated_Hole_D2.0mm
U50: BUF634AIDDAR; SOIC-8-1EP_3.9x4.9mm_P1.27mm_EP2.514x3.2mm_ThermalVias; Mouser Part Number 595-BUF634AIDDAR
U53: TPS560200; SOT-23-5
U54: LM1117MP-3.3; SOT-223-3_TabPin2

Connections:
+3V3: C228.2, C229.2, TP13.1, U54.2 (VO); also elsewhere on the board
+5V: C223.2, C224.2, C225.2, C226.2, C227.2, L1.2, R407.1, TP12.1, U54.3 (VI); also elsewhere on the board
+12V: C217.2, C219.2, C221.2, J29.9, J29.10, J44.1, J45.9, J45.10, R405.2, TP7.1, U50.7 (V+), U50.8 (NC_3), U53.1 (EN), U53.4 (VIN); also elsewhere on the board
-12V: C218.1, C220.1, C222.1, J29.1, J29.2, J44.2, J45.1, J45.2, R406.1, TP9.1, U50.4 (V-), U50.9 (EP); also elsewhere on the board
GNDREF: C217.1, C218.2, C219.1, C220.2, C221.1, C222.2, C223.1, C224.1, C225.1, C226.1, C227.1, C228.1, C229.1, J29.3, J29.4, J29.5, J29.6, J29.7, J29.8, J45.3, J45.4, J45.5, J45.6, J45.7, J45.8, R408.2, TP8.1, U50.6 (VO), U53.2 (GND), U54.1 (GND); also elsewhere on the board
unnamed: J29.11, J29.12
unnamed: J29.13, J29.14
unnamed: J29.15, J29.16
unnamed: R405.1, R406.2, U50.3 (VIN)
unnamed: R407.2, R408.1, U53.5 (FB)
unnamed: L1.1, U53.3 (PH)

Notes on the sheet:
EuroRack Power Headers
24V Input
Gate
3.3V Ldo
+5V
BUG634 Driver for main synth
12-5V Buck Switcher

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
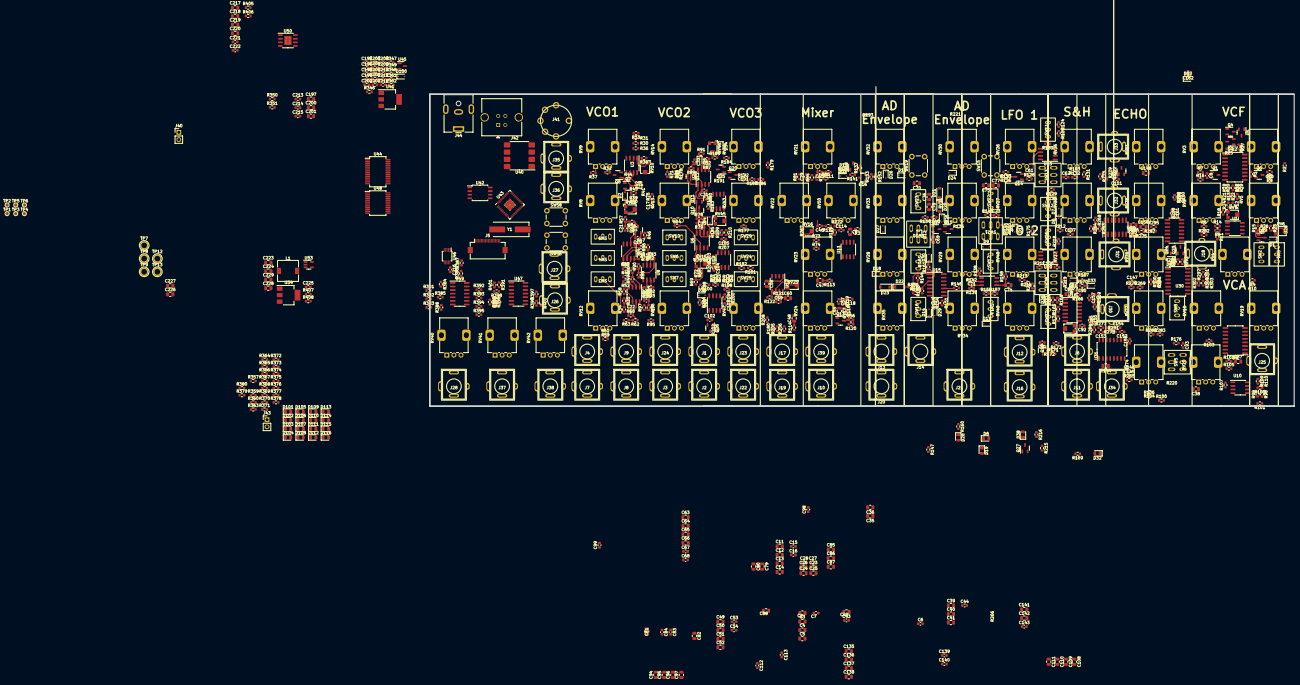
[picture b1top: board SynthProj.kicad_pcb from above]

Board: 4 copper layers, 304.8 x 110.0 mm, 751 parts (0 on the bottom side), 449 nets.

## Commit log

2023-11-26 init commit
2023-11-27 more work...
2023-11-28 finishing schematic 1.0
2023-11-28 added schematics
2023-11-29 Doing some layout
2023-11-29 added stp for pot
2023-12-01 doing some routing - split sequencer into another project
2023-12-02 routing work...
2023-12-02 more routing...
2023-12-02 routing... placing... going cross eyed...
2023-12-02 work
2023-12-02 updated license to cern ohl v2
2023-12-03 lots of routes, added vco3, lfo2.
2023-12-03 more and more routing
2023-12-03 my back hurts im routing so much
2023-12-04 800 unrouted nets
2023-12-04 under 600 unrouted nets!
2023-12-04 more work
2023-12-05 routing microcontroller
2023-12-06 more and more and more and more and more routing
2023-12-18 Removed microcontroller and power stuff to simplify
2023-12-21 finished routing!
2023-12-21 updated placement & routing
2023-12-22 drc checking and nudging
2023-12-24 misc commit
2023-12-25 i cant remember
2023-12-27 added manufacturing files
2023-12-27 misc.
2023-12-28 jlc files.
2023-12-31 created manufacturing files
2024-01-02 creating faceplate files...
2024-01-02 mixed files around... fixed mistake
2024-01-02 working on face plate.
2024-01-04 completed synth and face plate... ready to order...
